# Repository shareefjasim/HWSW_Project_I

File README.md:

# Wi-Fi Crowdness & Help Button System

## 1. High-Level Overview

### Project Title: **Wi-Fi Crowdness & Help Button System**

### What It Does
This project consists of two devices communicating over Wi-Fi:

1. **Help Button Device**:
   - Counts people passing by using a sensor.
   - Provides a help button for customers to request assistance.
   - Lights up an LED once the help request is acknowledged by the Monitor Device.

2. **Monitor Device**:
   - Aggregates data from multiple Help Button Devices.
   - Displays the crowdness level on a stepper-motor gauge.
   - Provides a screen interface for more detailed data and insights.

### General Sketch (Highlighting Physical Features)
#### Help Button Device:
- **Wi-Fi MCU**
- **People-Counting Sensor** (ToF/PIR)
- **Button** (Request Help)
- **LED** (Help Confirmation)

#### Monitor Device (Console):
- **Wi-Fi MCU**
- **Screen** (UI + Data from Help Devices)
- **Stepper-Motor Gauge** (Crowdness Level)
- Optional **Button** for staff interactions

---

## 2. Help Button Device

### Detailed Sketch

### How It Works
- **People-Counting Sensor**:
  - Uses a Time-of-Flight sensor (e.g., ST VL53L1X) or a simple PIR motion sensor to detect and count passersby in real time.
- **Help Button**:
  - When pressed, it sends a "HELP_REQUEST" message over Wi-Fi to the Monitor Device.
- **LED**:
  - Lights up once the Monitor Device acknowledges the request (confirmation message: “Help is on the way”).
- **Wi-Fi MCU**:
  - Aggregates data from the sensor and the button, and sends it periodically or on events to the Monitor Device.

---

## 3. Monitor Device

### Detailed Sketch

### How It Works
- **Wi-Fi MCU**:
  - Connects to the local network and receives data from multiple Help Button Devices.
  - Aggregates:
    - **People Counts** to gauge aisle/store section busyness.
    - **Help Requests** to see customer needs.
- **Screen**:
  - Displays a user interface with detailed stats (e.g., people counts, help requests, aisle name).
- **Stepper Motor Gauge**:
  - Reflects the overall crowdness level (0–100 scale).
  - Higher values indicate increased foot traffic, helping allocate more staff.
- **Optional Button**:
  - Allows staff to confirm requests or navigate menu items.

---

## 4. Communication & System Diagram

### Communication Workflow (Figure A)

---

## 5. Hardware Choices & Part Numbers

### Help Button Device
| **Component**            | **Description**                                                                 |
|--------------------------|---------------------------------------------------------------------------------|
| **Wi-Fi MCU**            | ESP32-WROOM-32 or ESP8266-based modules                                        |
| **Sensor**               | ST VL53L1X (Time-of-Flight, accurate short-to-mid range) or PIR motion sensor |
| **Button**               | Generic tactile push-button                                                   |
| **LED**                  | 5 mm LED with a current-limiting resistor                                      |
| **Power Supply**         | Lithium-ion battery + AMS1117-3.3 voltage regulator                           |

### Monitor Device
| **Component**            | **Description**                                                                 |
|--------------------------|---------------------------------------------------------------------------------|
| **Wi-Fi MCU**            | ESP32-WROOM-32 or ESP8266-based modules                                        |
| **Screen**               | 7.0" TFT LCD with ILI9488 or RA8875 controller (800x480 or 1024x600 resolution) |
| **Stepper Motor**        | 28BYJ-48 stepper motor with ULN2003 driver or NEMA17 with A4988 driver         |
| **Power Supply**         | USB power adapter or lithium-ion battery pack                                  |

---

## 6. Installation and Usage

1. **Clone the Repository**:
   ```bash
   git clone https://github.com/yourusername/HWSW_Project_I.git

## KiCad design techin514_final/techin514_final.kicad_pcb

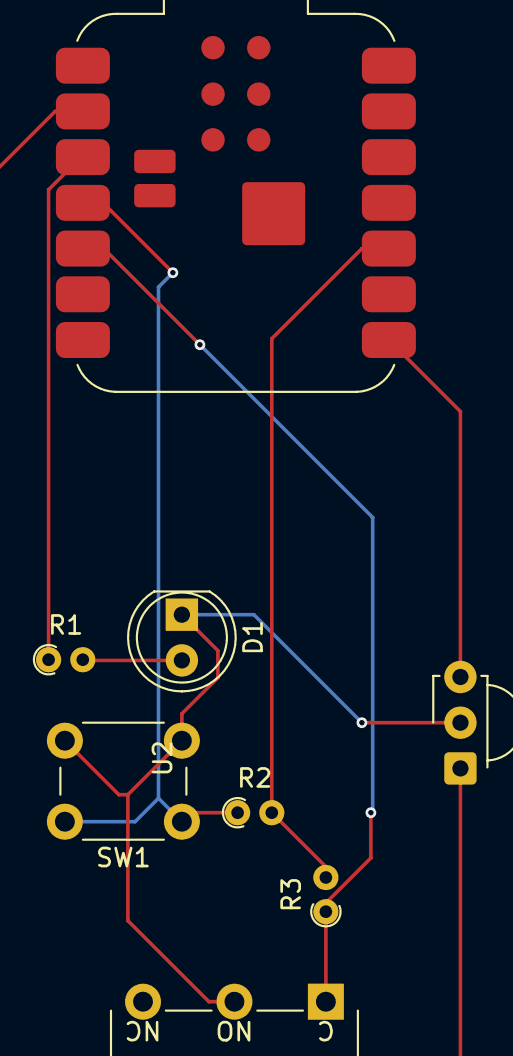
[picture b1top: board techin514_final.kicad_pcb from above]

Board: 2 copper layers, 8 parts (0 on the bottom side), 8 nets.

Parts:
D1: SFH4546; LED_D5.0mm_IRGrey
EXP32_c3: MCU_Seeed_ESP32C3
R1: 220 Ω; R_Axial_DIN0204_L3.6mm_D1.6mm_P1.90mm_Vertical
R2: 10K; R_Axial_DIN0204_L3.6mm_D1.6mm_P1.90mm_Vertical
R3: 10k; R_Axial_DIN0204_L3.6mm_D1.6mm_P1.90mm_Vertical
SW1: SW_Push_Dual_x2; SW_PUSH_6mm_H4.3mm
SW2: SW_Push_Dual_x2; SW_XKB_DM1-16UC-1
U2: HC‑SR501 Sensor Board; Vishay_MINICAST-3Pin

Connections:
unnamed: EXP32_c3.8 (5V), U2.3 (Vs)
unnamed: D1.1 (K), SW1.2 (D), SW2.2 (D), U2.2 (GND)
unnamed: D1.2 (A), R1.2
unnamed: EXP32_c3.10 (3V3), R2.2, R3.2
unnamed: EXP32_c3.2 (GPIO2_A1_D1), U2.1 (OUT)
unnamed: EXP32_c3.3 (GPIO3_A2_D2), R1.1
unnamed: EXP32_c3.4 (GPIO4_A3_D3), R2.1, SW1.1 (C)
unnamed: EXP32_c3.5 (GPIO4_A3_D3_SDA), R3.1, SW2.1 (C)

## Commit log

2025-01-22 init
2025-01-29 initSchematic
2025-01-31 Markup Readme
2025-02-21 sense init code
